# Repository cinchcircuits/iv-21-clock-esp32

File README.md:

# iv-21-clock-esp32
Basic clock designed around a IV-21 FL tube

# Attributions
- This project was largely mutated from [sjm4306s project](https://hackaday.io/project/167749-tiny-iv-21-vfd-clock)
- The max6921 control code was borrowed from [DellaRaccoon](https://github.com/DellaRaccoon/vfd-control/tree/master)
- the mcp3x21 code was pulled from "Andon", I do not recall where I found it.
- As always, many thanks to [Adafruit](https://www.adafruit.com/) for all of their contributions to circuit python

# What is on the board
- A FL tube, a IV-21
- XIAO board. I am using a ESP32C3, but many micro controllers work
- mcp3x21 A2D converter for getting feedback of the drive voltage for the device 

# Design files
Find the board files [Here](eagle-files)

# Case cad files
I made a simple case for this device in Fusion 360. 
All files are avaliable [Here](case-cad)

# Code
The esp32 code can be found [here](esp32-code)

This code is still a WIP. It doesn't do more than display some numbers.

Most of the code development tims so far was just in getting the dc-2-dc circuit working correctly.

This is an image of the clock running:

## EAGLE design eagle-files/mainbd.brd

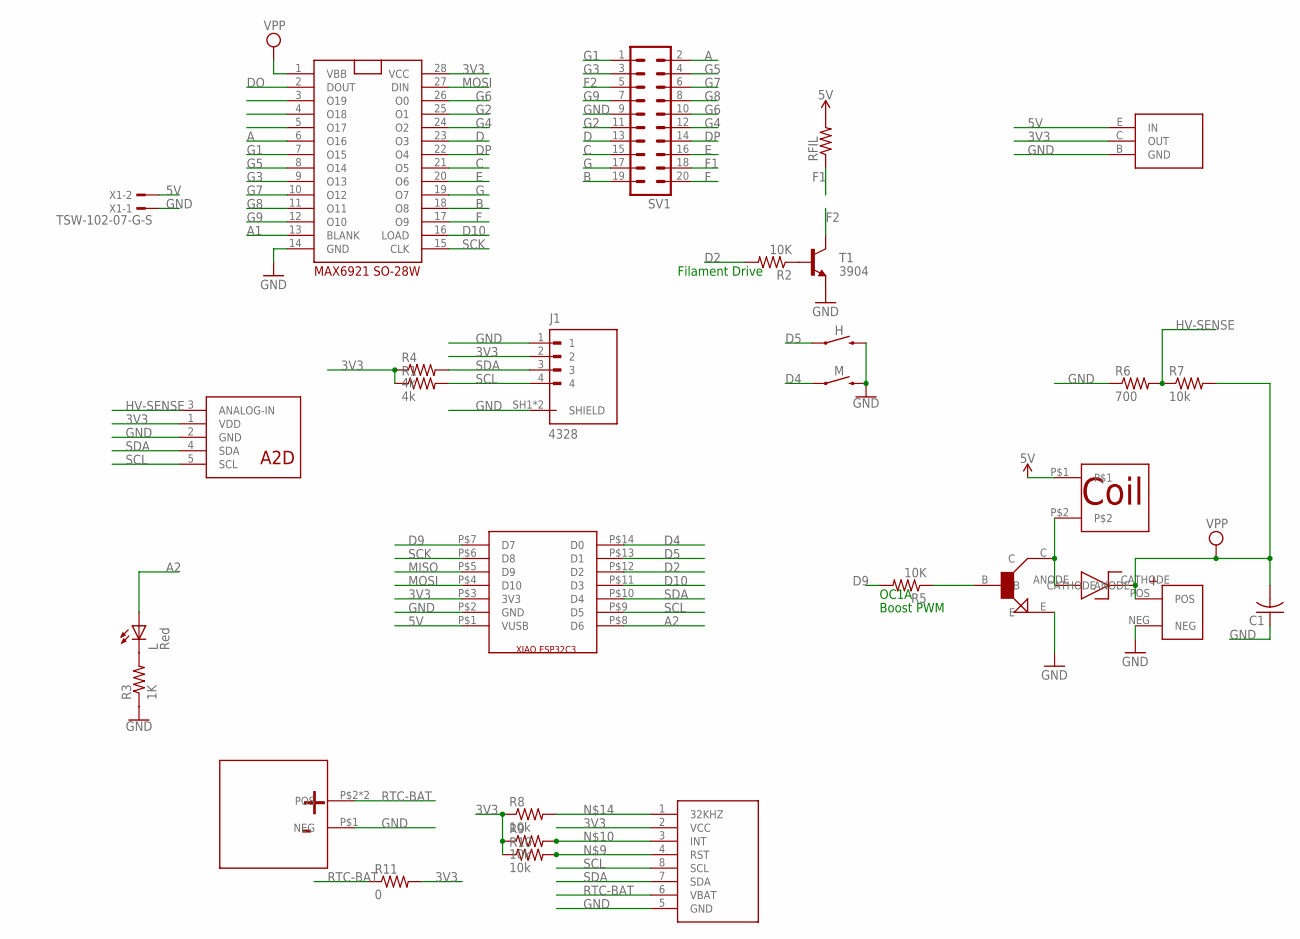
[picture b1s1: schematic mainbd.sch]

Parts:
3.3V-LDO: LDO-3.3V-AZ1117CR-3.3TRG1; SOT89-BCE
.: NPN-2SCR513P5; SOT89-BCE
C1: C-USC0805; C0805
H: MOMENTARY-SWITCH-SPST-PTH-RIGHT-ANGLE-KIT; TACTILE_SWITCH_PTH_RIGHT_ANGLE_KIT
J1: 4328; ADAFRUIT_4328
L: Red; CHIP-LED0805
M: MOMENTARY-SWITCH-SPST-PTH-RIGHT-ANGLE-KIT; TACTILE_SWITCH_PTH_RIGHT_ANGLE_KIT
R1, R4: 4k; R0805W
R2, R5: 10K; M0805
R3: 1K; M0805
R6: 700; R0805W
R7: 10k; R0805W
R8, R9, R10: 10k; M0805
R11: 0; M0805
RFIL: FLIPFLOP-RES; 0805-THM
SV1: MA10-2
T1: 3904; SOT23-BEC
U$1: MAX6921; SO28W
U$3: DS3231M; SOIC8
U$4: CAP-330
U$5: BATTERY-2998-COIN
U$6: INDUCTOR-453226
U$7: XIAOESP32C3
U$8: A2D-MCP3221A6T; SOT23-5
U$9: DIODE-ZENIER-CMSH1-20MLTR13; SMA-DIODE
X1: TSW-102-07-G-S; TSW-102-XX-G-S

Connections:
3V3: 3.3V-LDO.C (OUT), J1.2, R1.1, R4.1, R8.1, R9.1, R10.1, R11.2, U$1.28 (VCC), U$3.2 (VCC), U$7.P$3 (3V3), U$8.1 (VDD)
5V: 3.3V-LDO.E (IN), RFIL.2, U$6.P$1, U$7.P$1 (VUSB), X1.2
A: SV1.2, U$1.6 (O16)
A1: U$1.13 (BLANK)
A2: L.A, U$7.P$8 (D6)
B: SV1.19, U$1.18 (O8)
C: SV1.15, U$1.21 (O5)
D: SV1.13, U$1.23 (O3)
D2: R2.2, U$7.P$12 (D2)
D4: M.1, U$7.P$14 (D0)
D5: H.1, U$7.P$13 (D1)
D9: R5.2, U$7.P$7 (D7)
D10: U$1.16 (LOAD), U$7.P$11 (D3)
DO: U$1.2 (DOUT)
DP: SV1.14, U$1.22 (O4)
E: SV1.16, U$1.20 (O6)
F: SV1.20, U$1.17 (O9)
F1: RFIL.1, SV1.18
F2: SV1.5, T1.C
G: SV1.17, U$1.19 (O7)
G1: SV1.1, U$1.7 (O15)
G2: SV1.11, U$1.25 (O1)
G3: SV1.3, U$1.9 (O13)
G4: SV1.12, U$1.24 (O2)
G5: SV1.4, U$1.8 (O14)
G6: SV1.10, U$1.26 (O0)
G7: SV1.6, U$1.10 (O12)
G8: SV1.8, U$1.11 (O11)
G9: SV1.7, U$1.12 (O10)
GND: 3.3V-LDO.B (GND), ..E, C1.1, H.2, J1.1, J1.SH1 (SHIELD), J1.SH2 (SHIELD), M.2, R3.1, R6.1, SV1.9, T1.E, U$1.14 (GND), U$3.5 (GND), U$4.NEG, U$5.P$1 (NEG), U$7.P$2 (GND), U$8.2 (GND), X1.1
HV-SENSE: R6.2, R7.1, U$8.3 (ANALOG-IN)
MISO: U$7.P$5 (D9)
MOSI: U$1.27 (DIN), U$7.P$4 (D10)
unnamed: L.C, R3.2
unnamed: ..B, R5.1
unnamed: ..C, U$6.P$2, U$9.ANODE
unnamed: R10.2, U$3.4 (RST)
unnamed: R9.2, U$3.3 (INT)
unnamed: R8.2, U$3.1 (32KHZ)
unnamed: R2.1, T1.B
RTC-BAT: R11.1, U$3.6 (VBAT), U$5.P$2 (POS), U$5.P$3 (POS)
SCK: U$1.15 (CLK), U$7.P$6 (D8)
SCL: J1.4, R1.2, U$3.8 (SCL), U$7.P$9 (D5), U$8.5 (SCL)
SDA: J1.3, R4.2, U$3.7 (SDA), U$7.P$10 (D4), U$8.4 (SDA)
VPP: C1.2, R7.2, U$1.1 (VBB), U$4.POS, U$9.CATHODE

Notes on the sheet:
Filament Drive
OC1A
Boost PWM

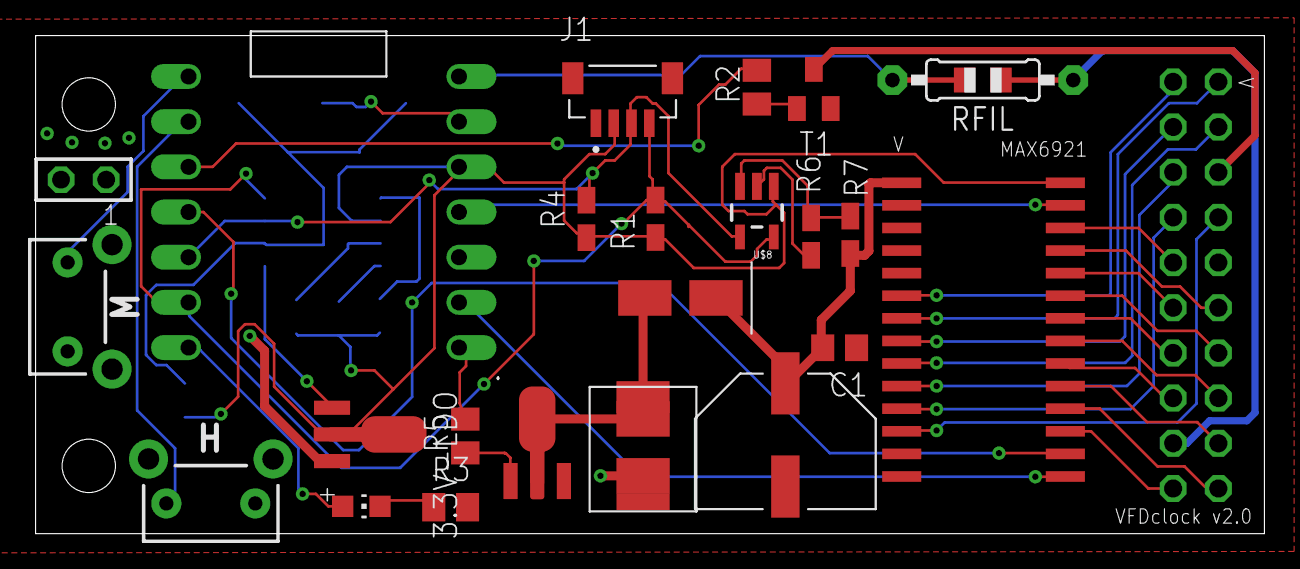
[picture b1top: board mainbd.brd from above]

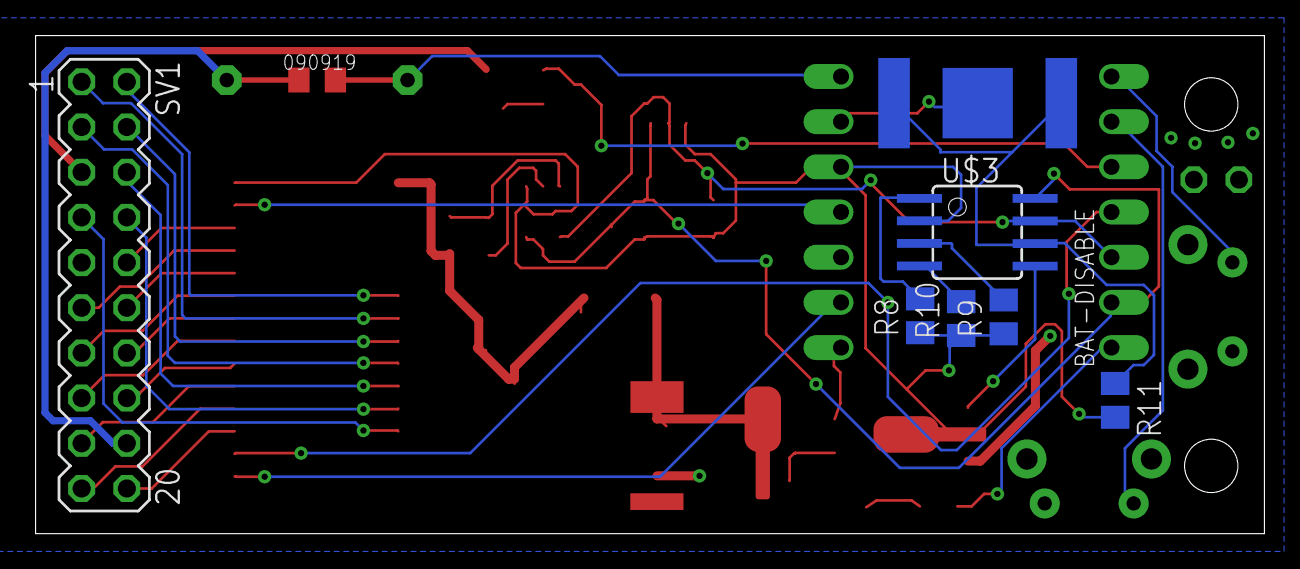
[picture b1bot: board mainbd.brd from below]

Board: 2 copper layers, 69.1 x 28.0 mm, 31 parts (7 on the bottom side), 42 nets.

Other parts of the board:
U$2: SJM4306_SMALL_NO_MASK

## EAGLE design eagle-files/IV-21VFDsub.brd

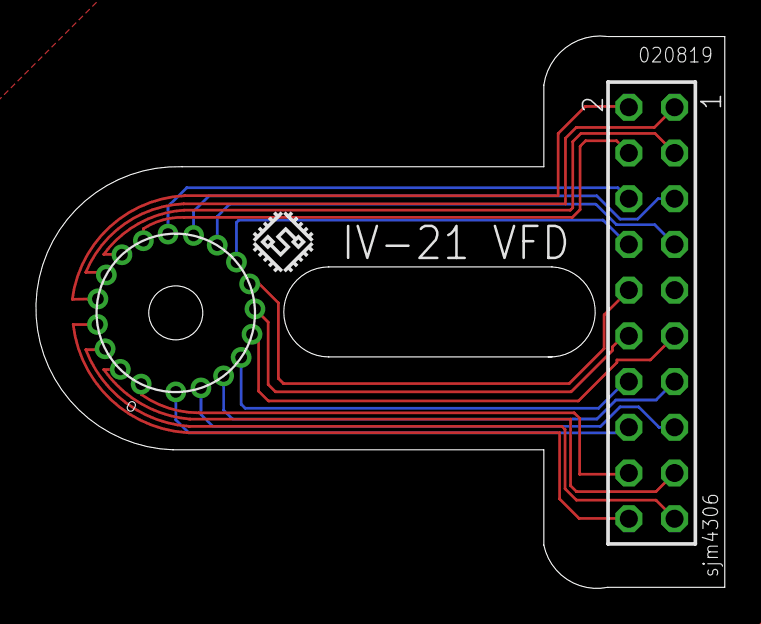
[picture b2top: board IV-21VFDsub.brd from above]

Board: 2 copper layers, 38.3 x 30.7 mm, 4 parts (1 on the bottom side), 19 nets.

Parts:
U$1: IV-21VFD
U$2, U$3: SJM4306_LOGO_SMALL
X1: TSW-110-07-G-D; TSW-110-XX-G-D

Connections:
A: U$1.P$5, X1.2
B: U$1.P$3, X1.19
C: U$1.P$18, X1.15
D: U$1.P$17, X1.13
DP: U$1.P$16, X1.14
E: U$1.P$19, X1.16
F: U$1.P$4, X1.20
F1: U$1.P$1, X1.18
F2: U$1.P$10, X1.5
G: U$1.P$2, X1.17
G1: U$1.P$6, X1.1
G2: U$1.P$15, X1.11
G3: U$1.P$7, X1.3
G4: U$1.P$14, X1.12
G5: U$1.P$8, X1.4
G6: U$1.P$13, X1.10
G7: U$1.P$9, X1.6
G8: U$1.P$12, X1.8
G9: U$1.P$11, X1.7

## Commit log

2025-03-15 Adding eagle files
2025-03-15 Initial files
2025-03-15 Adding a basic image
2025-03-15 Added a basic readme
2025-03-15 Added an image link to the readme
2025-03-15 Adding pinout notes
2025-03-16 Making the code act like a very basic clock.
2025-03-16 Moving componets around a little bit to better accomidate xaio board
2025-03-26 cleaned up code a bit. Changed time format
2025-03-26 Adding DST BS
2025-03-26 Adding test code
2025-03-26 git add HV check code
2025-04-01 Fixing a few bugs, one involving ntp timeoits
2025-04-01 etting just a zero return when the ntp update fails
2025-04-09 Switching to a better image of the clock
2025-04-09 Altering Readme a bit, uploading more complete libs
2025-04-09 Adding CAD files from the basic case
2025-04-18 Statring work on adding IV-18 support
2025-04-18 Adding cam file for production
2025-04-18 final tweak to one track on iv-18 brd

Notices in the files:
parts and their libraries:
SparkFun-Switches: Licensing: Creative Commons ShareAlike 4.0 International - https://creativecommons.org/licenses/by-sa/4.0
